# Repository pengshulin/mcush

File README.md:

DESCRIPTION
===========
* MCUSH is the short name for MCU-SHell.
* A practical project that enhance microcontroller serial port console with shell features like in many linux systems.
* The goal of the project is to provide a firmware template that will expand commands for new applications, so it should be designed with simple API and easy to use.
* Initially developed on FreeRTOS, but with os abstract layer, MCUSH has been ported to other RTOSes.
* The core shell runs as a stand-alone task with middle level priority.
* Auxiliary micro service tasks can be chosen when you need, such as LED blinker, logger, soft-watchdog...
* Test suites and templates written in python are privided to ease the test work and create CLI/GUI applications.
* Hosted on github: <https://github.com/pengshulin/mcush>
* Python core module released on PYPI and installed by 'pip3 install mcush'

FEATURES
========
* SUPPORT:
  * command functions are called with arguments in form of argc and argv
  * arguments parser with short option '-' and long option '--'
  * low memory requirement, suitable for some tiny chips
  * prompt hook function for customize
  * compact history command list
  * multi-line input
  * may port to different architectures, but currently it runs on CORTEX-M only
* NOT SUPPORT:
  * lineedit features that require multi-bytes (such as array keys, shell colors...) are not supported, only simple features that require single-byte (such as BACKSPACE, Ctrl-A/B/C/D/E/F/K/N/P) are supported

ROADMAP
=======
(todo/in progress)
* add threadx/chibios/liteos/zephyr/osek port
* test embedded dynamic languages (eg. lua/picolisp/tinyscheme/ulisp/micropython...)
* add practical utilities, such as network (traceroute, ntp client...)

ENVIRONMENT
===========
* arm-none-eabi-gcc, newlibc, arm-none-eabi-gdb, cgdb
* scons + personal MCU build scripts
  <https://github.com/pengshulin/site_scons>
* STLink v2 + st-flash(flasher) + st-util(gdb server)
  <https://github.com/texane/stlink>
* openocd
* develope and test on Debian/Ubuntu machines

RESOURCES
=========
* Snapshots: <https://github.com/pengshulin/mcush/tree/master/snapshots> 
* Demo videos: <https://github.com/pengshulin/mcush/tree/master/demo_video>  Suitable for beginners and give you a brief overview.
* Windows/VCP(Virtual Com Port) driver: <https://github.com/pengshulin/mcush/tree/master/vcp_driver>

HARDWARE
========
* tiny controller: <https://github.com/pengshulin/mcush/tree/master/hardware_tiny>
* Shell-Lab series controllers: <http://www.linkongsoft.com/shell-lab/>
* Vibration Analysis Platform: <http://www.linkongsoft.com/vap/>

LICENSE
=======
* source codes:
  * As this is my personal software toolkit, you can use it freely only for non-commercial purpose.
  * Contact the author for commercial authorization, or it's NOT AUTHORIZED.
* binary executables:
  * images provided in build directory are free as BSD
* hardware design files:
  * similar to the source codes: need commercial authorization

COMMERCIAL
==========
Contact Shanghai Linkong Software Technologies Co., Ltd for commerical support.
http://www.linkongsoft.com/

AUTHOR
======
Peng Shulin <trees_peng@163.com>
Shanghai, China 2022

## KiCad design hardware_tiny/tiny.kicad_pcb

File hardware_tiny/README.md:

RESOURCES
=========
* Demo videos: <https://github.com/pengshulin/mcush/tree/master/demo_video>
* Windows/VCP(Virtual Com Port) driver: <https://github.com/pengshulin/mcush/tree/master/vcp_driver>
* Schematic: <https://github.com/pengshulin/mcush/blob/master/hardware_tiny/tiny.pdf>
* Latest firmware: <https://github.com/pengshulin/mcush/tree/master/hardware_tiny/build>

LICENSE
=======
* see the project LICENSE

AUTHOR
======
Peng Shulin <trees_peng@163.com>
Shanghai, China 2018

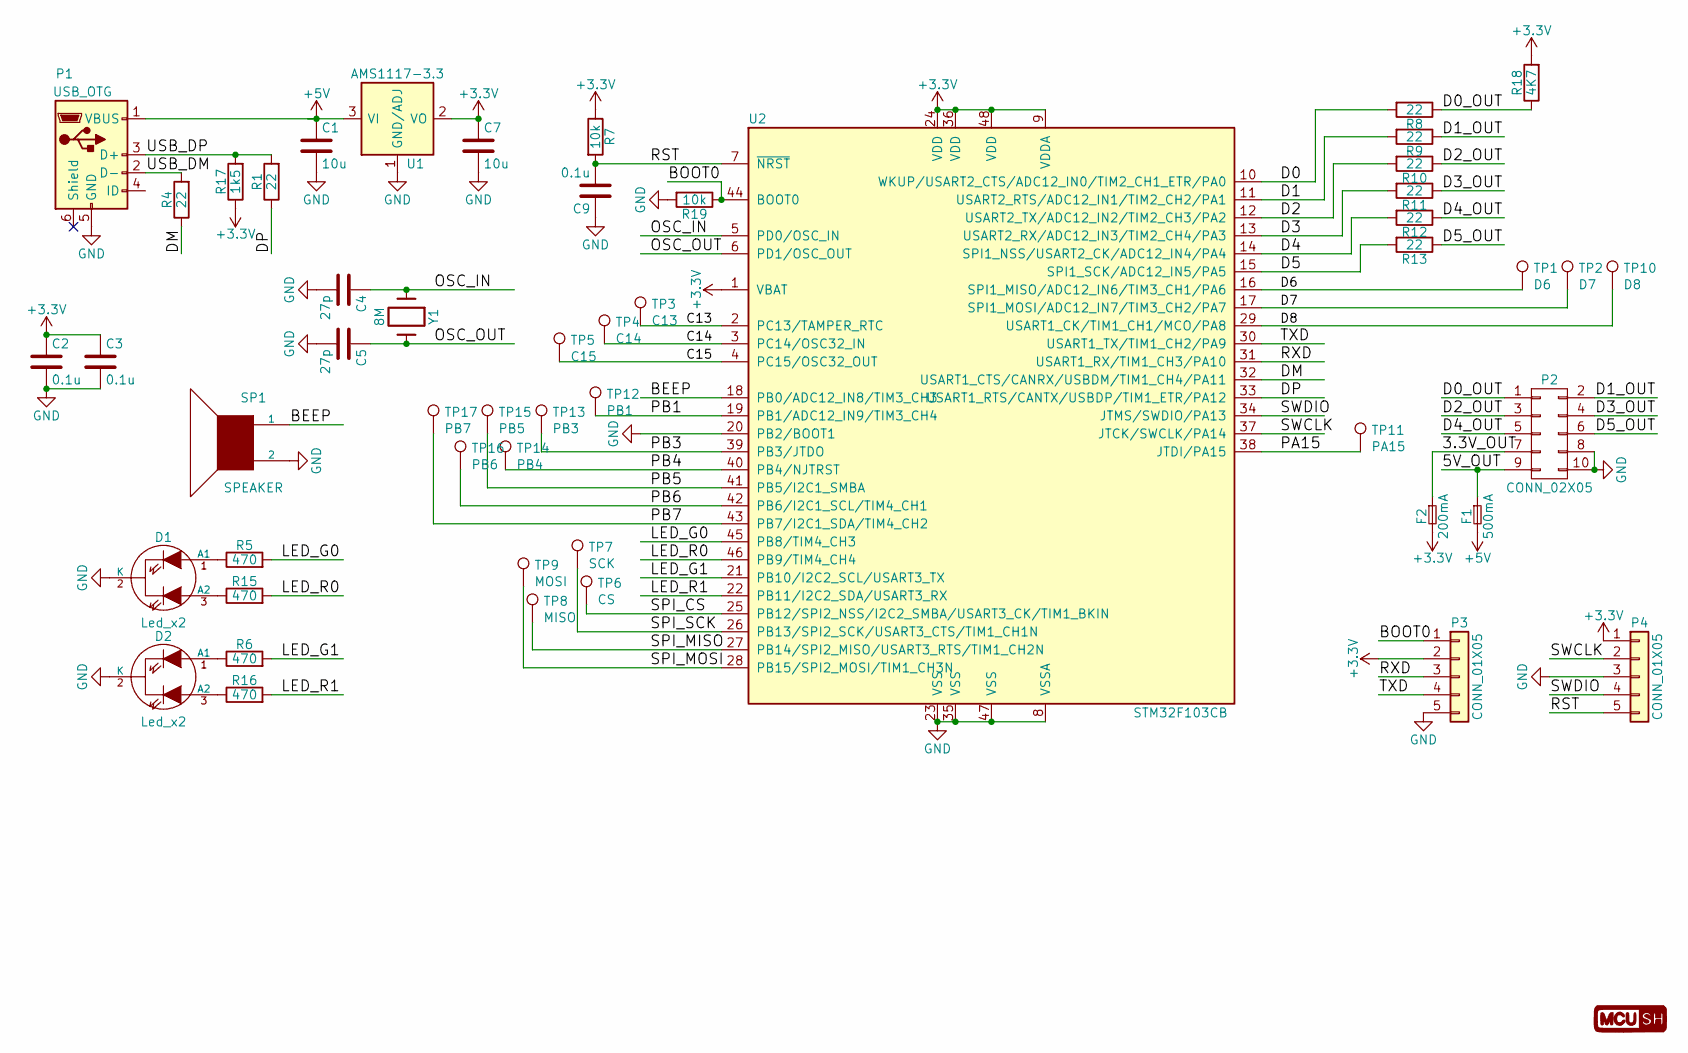
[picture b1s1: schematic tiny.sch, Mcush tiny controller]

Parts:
C1, C7: 10u; C_1210_3225Metric_Pad1.42x2.65mm_HandSolder
C2, C3, C9: 0.1u; C_0805_2012Metric_Pad1.15x1.40mm_HandSolder
C4, C5: 27p; C_0805_2012Metric_Pad1.15x1.40mm_HandSolder
D1, D2: Led_x2; LEDx2-3MM
F1: 500mA; R_1210_3225Metric_Pad1.42x2.65mm_HandSolder
F2: 200mA; R_1210_3225Metric_Pad1.42x2.65mm_HandSolder
LOGO1: MCUSH; mcush_txt_logo
P1: USB_OTG; USB_Mini-B_HandSoldering
P2: CONN_02X05; IDC10-E
P3, P4: CONN_01X05; PinHeader_1x05_P2.54mm_Vertical
R1, R4, R8, R9, R10, R11, R12, R13: 22; R_0805_2012Metric_Pad1.15x1.40mm_HandSolder
R5, R6, R15, R16: 470; R_0805_2012Metric_Pad1.15x1.40mm_HandSolder
R7, R19: 10k; R_0805_2012Metric_Pad1.15x1.40mm_HandSolder
R17: 1k5; R_0805_2012Metric_Pad1.15x1.40mm_HandSolder
R18: 4K7; R_0805_2012Metric_Pad1.15x1.40mm_HandSolder
SP1: SPEAKER; Buzzer_9x4.2RM4
TP1: D6; TestPoint_Pad_D1.0mm
TP2: D7; TestPoint_Pad_D1.0mm
TP3: C13; TestPoint_Pad_D1.0mm
TP4: C14; TestPoint_Pad_D1.0mm
TP5: C15; TestPoint_Pad_D1.0mm
TP6: CS; TestPoint_Pad_D1.0mm
TP7: SCK; TestPoint_Pad_D1.0mm
TP8: MISO; TestPoint_Pad_D1.0mm
TP9: MOSI; TestPoint_Pad_D1.0mm
TP10: D8; TestPoint_Pad_D1.0mm
TP11: PA15; TestPoint_Pad_D1.0mm
TP12: PB1; TestPoint_Pad_D1.0mm
TP13: PB3; TestPoint_Pad_D1.0mm
TP14: PB4; TestPoint_Pad_D1.0mm
TP15: PB5; TestPoint_Pad_D1.0mm
TP16: PB6; TestPoint_Pad_D1.0mm
TP17: PB7; TestPoint_Pad_D1.0mm
U1: AMS1117-3.3; SOT-223-3_TabPin2
U2: STM32F103CB; LQFP-48_7x7mm_P0.5mm
Y1: 8M; Crystal_HC49-U_Vertical

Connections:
+3V3: C2.1, C3.1, C7.1, F2.2, P3.2, P4.1, R7.1, R17.1, R18.2, U1.2 (VO), U2.1 (VBAT), U2.9 (VDDA), U2.24 (VDD), U2.36 (VDD), U2.48 (VDD)
+5V: C1.1, F1.2, P1.1 (VBUS), U1.3 (VI)
/3.3V_OUT: F2.1, P2.7
/5V_OUT: F1.1, P2.9
/BEEP: SP1.1, U2.18 (PB0/ADC12_IN8/TIM3_CH3)
/BOOT0: P3.1, R19.1, U2.44 (BOOT0)
/C13: TP3.1, U2.2 (PC13/TAMPER_RTC)
/C14: TP4.1, U2.3 (PC14/OSC32_IN)
/C15: TP5.1, U2.4 (PC15/OSC32_OUT)
/D0: R8.2, U2.10 (WKUP/USART2_CTS/ADC12_IN0/TIM2_CH1_ETR/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)
/D0_OUT: P2.1, R8.1, R18.1
/D1: R9.2, U2.11 (USART2_RTS/ADC12_IN1/TIM2_CH2/PA1)
/D1_OUT: P2.2, R9.1
/D2: R10.2, U2.12 (USART2_TX/ADC12_IN2/TIM2_CH3/PA2)
/D2_OUT: P2.3, R10.1
/D3: R11.2, U2.13 (USART2_RX/ADC12_IN3/TIM2_CH4/PA3)
/D3_OUT: P2.4, R11.1
/D4: R12.2, U2.14 (SPI1_NSS/USART2_CK/ADC12_IN4/PA4)
/D4_OUT: P2.5, R12.1
/D5: R13.2, U2.15 (SPI1_SCK/ADC12_IN5/PA5)
/D5_OUT: P2.6, R13.1
/D6: TP1.1, U2.16 (SPI1_MISO/ADC12_IN6/TIM3_CH1/PA6)
/D7: TP2.1, U2.17 (SPI1_MOSI/ADC12_IN7/TIM3_CH2/PA7)
/D8: TP10.1, U2.29 (USART1_CK/TIM1_CH1/MCO/PA8)
/DM: R4.1, U2.32 (USART1_CTS/CANRX/USBDM/TIM1_CH4/PA11)
/DP: R1.1, U2.33 (USART1_RTS/CANTX/USBDP/TIM1_ETR/PA12)
/LED_G0: R5.2, U2.45 (PB8/TIM4_CH3)
/LED_G1: R6.2, U2.21 (PB10/I2C2_SCL/USART3_TX)
/LED_R0: R15.2, U2.46 (PB9/TIM4_CH4)
/LED_R1: R16.2, U2.22 (PB11/I2C2_SDA/USART3_RX)
/OSC_IN: C4.1, U2.5 (PD0/OSC_IN), Y1.1
/OSC_OUT: C5.1, U2.6 (PD1/OSC_OUT), Y1.2
/PA15: TP11.1, U2.38 (JTDI/PA15)
/PB1: TP12.1, U2.19 (PB1/ADC12_IN9/TIM3_CH4)
/PB3: TP13.1, U2.39 (PB3/JTDO)
/PB4: TP14.1, U2.40 (PB4/NJTRST)
/PB5: TP15.1, U2.41 (PB5/I2C1_SMBA)
/PB6: TP16.1, U2.42 (PB6/I2C1_SCL/TIM4_CH1)
/PB7: TP17.1, U2.43 (PB7/I2C1_SDA/TIM4_CH2)
/RST: C9.2, P4.5, R7.2, U2.7 (~NRST)
/RXD: P3.3, U2.31 (USART1_RX/TIM1_CH3/PA10)
/SPI_CS: TP6.1, U2.25 (PB12/SPI2_NSS/I2C2_SMBA/USART3_CK/TIM1_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)
/SPI_MISO: TP8.1, U2.27 (PB14/SPI2_MISO/USART3_RTS/TIM1_CH2N)
/SPI_MOSI: TP9.1, U2.28 (PB15/SPI2_MOSI/TIM1_CH3N)
/SPI_SCK: TP7.1, U2.26 (PB13/SPI2_SCK/USART3_CTS/TIM1_CH1N)
/SWCLK: P4.2, U2.37 (JTCK/SWCLK/PA14)
/SWDIO: P4.4, U2.34 (JTMS/SWDIO/PA13)
/TXD: P3.4, U2.30 (USART1_TX/TIM1_CH2/PA9)
/USB_DM: P1.2 (D-), R4.2
/USB_DP: P1.3 (D+), R1.2, R17.2
GND: C1.2, C2.2, C3.2, C4.2, C5.2, C7.2, C9.1, D1.2 (K), D2.2 (K), P1.5 (GND), P2.8, P2.10, P3.5, P4.3, R19.2, SP1.2, U1.1 (GND/ADJ), U2.8 (VSSA), U2.20 (PB2/BOOT1), U2.23 (VSS), U2.35 (VSS), U2.47 (VSS)
unnamed: D1.1 (A1), R5.1
unnamed: D1.3 (A2), R15.1
unnamed: D2.1 (A1), R6.1
unnamed: D2.3 (A2), R16.1

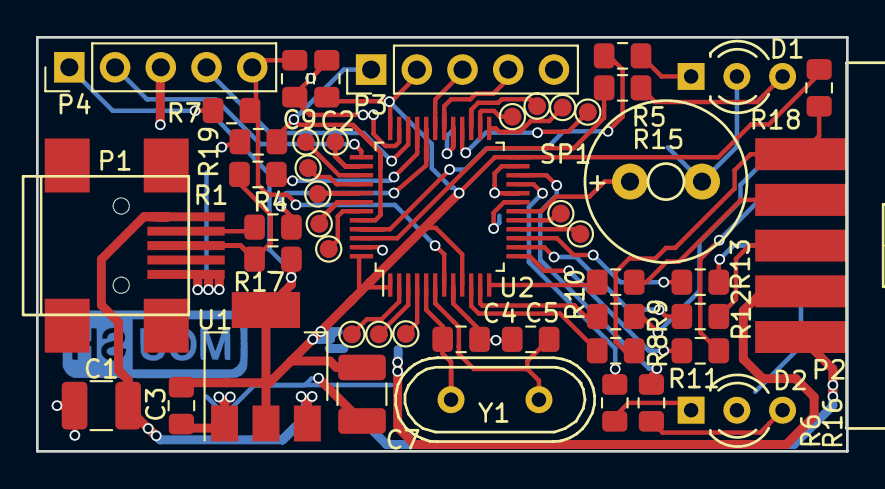
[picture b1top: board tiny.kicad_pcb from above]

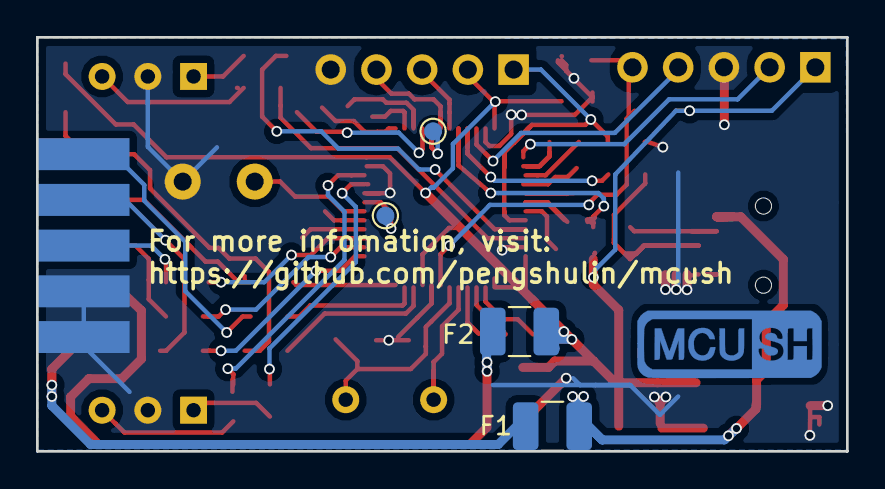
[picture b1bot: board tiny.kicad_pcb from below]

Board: 2 copper layers, 45.0 x 23.0 mm, 53 parts (5 on the bottom side), 55 nets.

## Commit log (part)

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2018-01-16 add: tjc hmi updater script
2018-01-18 edit
2018-02-13 add fcfs (Flash Configuration File System)
2018-02-23 fix the missing core direcotries
2018-03-06 fixbug: stm32f429ig flash 2M -> 1M actually
2018-03-07 fixbug: cat command, read mode, missing newline before prompt conditionally
2018-03-27 add shell_str.c
2018-05-02 add demo videos
2018-05-05 add resources url in readme
2018-05-07 add test max7219 script and demo video
2018-05-07 fix the spelling mistake
2018-05-09 add quoted arguments demo video
2018-05-12 add: hardware_usb_stick
2018-05-12 add build image for hardware_tiny board
2018-05-22 add cross build demo video
2018-06-20 add: appLwipDemo for stm32f407
2018-06-20 add: halstm32f207
2018-06-26 add customized scpi_idn mode
2018-06-27 add parson library
2018-07-05 add wget command
2018-07-07 edit: optimize opt_spec structure to reduze flash size
2018-07-12 edit:fix bugs checked by new gcc toolchain (imtroduced in ubuntu18.04
2018-07-13 edit:halt api optimize
2018-07-13 edit:remove all NON_OS feature
2018-07-13 fixbug:ENTER_CRITICAL before halt
2018-07-15 adapt for her scons api
2018-07-23 fixbug: opt parser for OPT_VALUE when USAGE_VALUE_REQUIRED is not set
2018-07-24 add: logger apis
2018-07-31 add: halstm32f103rb_nucleo
2018-08-10 add: lib crc and utils
2018-08-11 edit:add i2c lsb/nostop options and tested on tm1637 led controller
2018-08-13 fix: usb descriptor serial number sequence
2018-08-29 add_feature: check if command exists
2018-09-08 add tm1637 demo video
2018-09-14 add pwm/dxw90 micro servo demo
2018-09-20 add adc/pwm control
2018-10-06 add partial functions for gpio control
2018-10-10 add Dallas 1wire control; Tri-color LED control
2018-10-13 add official ST VCP v1.5.0
2018-10-16 add hardware tiny controller brocher
2018-10-19 add shell_call api
2018-10-26 add: HAL/LL Driver for STM32F4/7
2018-10-29 edit: rearrange the hal layer structure for better expandiability
2018-10-31 fixbug: hal_gpio/usart using ST/F1xx/HAL driver
2018-12-14 new logger policy
2018-12-17 edit: logger module use mutex for file manipulate
2018-12-18 fixbug: use spiffs_lock/unlock
2018-12-19 fixbug: deleted spiffs semaphore is invalid when format
2018-12-21 fixbug:logger line buffer too small to hold large contents
2018-12-24 edit: less malloc/free for log -t command
2018-12-27 fix: set_rtc_by_XXX accepts year in 2-digit; sys trace buffer bigger
2018-12-29 fixbug: dhcpc queue blocked
2019-01-01 add: sys idle_check/vfs_stat command; optimize: spiffs fd/cache size; fix: vfs open/close reentrance problem; optimize: app_logger lazy close
2019-01-01 add: some filesystem test scripts
2019-01-03 fixbug: increase local port for next tcp_bind
2019-01-03 fix: dhcpc discover timeout retry; add: net up/down/dhcp command
2019-01-05 add: logger new apis; lwip debug/logger; sprintf api with half integer feature; edit: lwip_bind_random ports rfc range
2019-01-06 edit: use native dhcp controller; add: netbiosns interface; fix: lwip_stats output directly to shell; edit: printf2 add hx/hX support;
2019-01-09 add: Mcush/wget function; lwip MEM_LIBC_MALLOC option defination;
2019-01-09 edit: set default MEM_MALLOC as lwip
2019-01-10 add: test wget command looply
2019-01-10 add: nc cmd for tcp debug;
2019-01-11 fix: clear wdg every digit blink; fix: wrong elf file searched in release mode; edit: increase default mcush stack
2019-01-11 optimize: cache nc send buffer for effeciency;
2019-01-14 fix: encoding err; edit: unified pdPASS return of QueueSend/Receive apis; change lan8742a delay function to rtos delay;
2019-01-18 add: configuration macro
2019-01-24 fix: release data bus on first half phrase when i2c read address ACK
2019-03-05 add: crc32 file check
2019-04-10 add spiflash chipid; add HAL_TEST_CLK_OUTPUT macro
2019-04-12 add modbus/tcp framework and demo hook functions
2019-04-29 add modbus/tcp features
2019-04-30 add_feature: modbus/tcp coil functions support
2019-05-06 fix: add timeout check for modbus/tcp connect (lazy check)
2019-05-13 fixbug: file not closed for crc check
2019-05-17 add one-wire for stm32f4; optimize rtc init policy
2019-06-05 update to FreeRTOS v10.2.1; add missing files
2019-06-18 edit: basic str translation embedded; add compare_functions
2019-06-24 add: fastlz lib
2019-07-10 add: alink test; ld scripts; edit rtc init algorithms; fix bugs
2019-07-11 optimze lan7820 driver; user sprintf_ip/mac api instead of logger_ip/mac
2019-07-14 add: alink readme/license file; fix some bugs
2019-07-23 add log_mon script
2019-08-02 fix: opt parse bug for single - parm condition; update debug utils
2019-08-07 optimize apis: shell_eval_xxx --> parse_xxx; split_line/strip_line; file_load_xxx;
2019-08-07 add switch random script
2019-08-20 add: lua gpio/log module
2019-08-31 add cmd option to dynamically edit dns; python module modification for Python v3; add python ledSet/Clr api; etc
2019-09-07 optimize lua module api
2019-09-09 fixbug: lua test example
2019-09-17 add missing libfatfs/source
2019-09-17 add fatfs port
2019-09-20 support multiple emulated spi modules
2019-09-24 add multi emulated i2c controllers support; fix _open return code on file error
2019-10-04 add stm32f429x_sdram.ld; fixbug for 32MBytes spiflash; ...
2019-10-04 add pre-built image for stm32f103c8 tiny boards
2019-10-08 add pulse generator command
2019-10-10 fix: led signal invert for board f103rc_mcudev
2019-10-10 add pre-built image for f103cb_tiny_controller; add step motor test script
2019-10-14 optimize i2c timing
2019-10-14 add SSD1306 controller and test script
2019-10-16 remove ds1w alias command
2019-10-20 emu_spi timing optimized; add MAX6675/TM7707 module; rebuild images
2019-10-22 rebuild images and remove .map files
2019-10-25 add AHT10 module; add max7219 8digits LED diaplay module; ...
2019-10-27 switch from py2exe to pyinstaller; add tag v1.4.3
2019-11-02 add instruments modules (fluke/keysight/uni_trend...); fix Aht10 bugs
2019-11-04 add FY6900 signal generator controller
2019-11-05 add meas/counter/sweep api for FY6900 module
2019-11-06 add Max30102 module
2019-11-07 add Ads1115 module
2019-11-10 optimzie shell lab api
2019-11-13 optimize F8808A apis
2019-11-24 add stm32f401cc/411ce WeAct board support
2019-11-24 add build images for stm32f401/411 WeAct boards
2019-12-05 add Korad/KA3005P 30V/5A power output
2019-12-06 fixbug: ka3005p output enable/disable api parms
2019-12-10 add rigol products templates
2020-01-13 add RIGOL/DS1000 Oscillator support
2020-02-13 add hal_key apis; add can baudrate api; add filter set command
2020-03-06 update ST_USB_FS_Device_Driver; ...
2020-03-17 add CAN drivers; update README for commerical support
2020-03-17 add libCanFestival
2020-04-01 spiffs chip-id optimize; add status read cmd; add Instrument class terminal_reset init option; add logger busy check api; ...
2020-04-10 add static task/queue create api; add support for stm32f030c8 tiny board; add python module Tongmen programmable power; ...
2020-04-20 fix: cache vcp linecoding setting (pyserial may raise exception in windows); optimize CAN api; add usb string descriptor configuration api from SConstruct; ...
2020-04-23 add ws2812 library and command; fixbug in fluke/f5520, print syntax in python v3; add missing files...
2020-04-24 fix: UniqueID address for stm32f030; default port/pin defination for ws2812 command
2020-04-26 optimize ws2812 apis
2020-04-27 add FCFS program api
2020-05-08 add enumPortsByClass api; ...
2020-05-08 fixbug: enumPortsByClass did not free serial port when IDNMatch error occurs
2020-05-10 optimize: use two default filters to receive all STD/EXT-ID frames; fix: check for Ctrl-C in can read command or *idn? may not work;
2020-05-13 fixbug for python3
2020-05-18 fixbug for Python V3
2020-05-18 add openocd/telnet api template
2020-05-19 add OpenOCD apis
2020-05-19 fixbug for pip setup.py
2020-05-26 optimize ws2812 push command and add fill command
2020-06-01 fixbug: stm32f103 hal/vcp driver; rebuild binaries; ...
2020-06-02 add ST/F0_HAL_Driver
2020-06-04 rename macro HAL_RESET_VCP_PIN -> HAL_RESET_USB_PINS
2020-06-15 optimize python api; remove crcmod module dependency
2020-06-15 add serial_send_bytes test script
2020-06-16 fixbug: ds1w/motion be compatiable in python v3
2020-06-26 add python readLine/writeCommand strip options
2020-07-16 add RTOS Abstract Layer; update STM32F7 HAL lib; add python lib for Miaoguan 485 Sensor
2020-07-17 impove RTOS Abstract Layer
2020-07-19 update CMSIS/lib; optimize OS Abstract Layer (split mutex from semaphore); add RTX port
2020-07-20 port RTOS Abstract Layer
2020-08-08 update CMSIS lib; add compiler port file; add more compiler check and fix those warnings; ...
2020-08-09 fix compiler warnings
2020-08-14 continue to port RTThread...
2020-08-17 add blink errno task brief instruction
2020-09-10 add mcush_os_none.h for special build condition(eg.bootloader); optimize ws2812 api; optimize logger.c build for when SPIFFS not supported; ...
2020-09-10 add libmd5 from lua/md5 projdct
2020-09-27 fixbug: script load command
2020-09-28 rebuild images for demo boards
2020-10-12 optimize os ports; optimize hal_gpio apis; remove wdg cmd; add (err)stop for script loading; add shortname check for help cmd;add down count option for lamp/strap python api; ...
2020-10-12 use independent basic hal api header file
2020-10-12 add missing documents
2020-10-13 fix: ignore timer_queue_overflow error for rtx port, or sys idle command will not work
2020-10-27 add python rotate mode control for ShellLabLamp
2020-11-25 add_lib: Mlx90614/ShellLabStepperMotor; optimize beep service task
2020-12-11 add WitMotion Python module
2020-12-19 add MindMotion MM32F031 support
2020-12-25 edit: reduce ws2812 buffer size; add sht30 sensor; add ShellLabSegmentDisplay support; ...
2021-02-19 add lpc43xx basic hal driver
2021-03-05 add GCode module to support Marlin firmware
2021-04-15 add inverse option for test command; rename Strap class to Strip; fixbug for FCFS/File in bytes mode; add new OS options; ...
2021-04-21 add MCUSH device API/C
2021-05-22 rebuild binaries; add device api for win32 support; ...
2021-05-22 add device/c api demoes
2021-05-24 add s1_relay_ctrl c/api demo
2021-06-06 fix parse_int error returns; add C/API test demo; add python SpotLightController module; update Ws2812 api;...
2021-06-12 add mcush_drv C++ driver and demo
2021-06-15 add Pca9685 module; add mcush_utils feature
2021-06-16 add mcush_util.dll build
2021-07-13 fix: CANOpen readObject command code
2021-08-21 add SN->MAC hash convert; redesign modbus/tcp data structure; modify VAP api; add RIGOL DG1022Z; fixbugs...
2021-08-22 modify blink errno reserved id; fix bugs ...
2021-09-02 update sys_arch_mcush for lwip; add heap check option for lwip cmd; replace address printf from %X to %p; modbus_tcp packet handler move to callback functions; ...
2021-09-02 add lwip/contrib-2.0.1
2021-09-12 move task_blink/logger/swdg into service directory
2021-09-15 add stm32g0xx support
2021-10-01 fix usb cdc/hid lib; add python modbus/sako/vap200-mqtt libs; ...
2021-10-13 add MCUSH software certification scan file
2021-11-16 add gpio pull-up/down for lpc845; add ShellLabHID class for simulator controller; add fast mode color switch for ShellLabLamp; add VAP200Extend; ...
2021-12-13 fixbug: F1/HAL; add:ShellLabKeySwitch Python class
2022-02-16 update libFreeRTOS to v10.4.6; update mcush_util
2022-02-17 update: mcush_util
2022-02-18 add_feature: mcush_util get_file and shell mode
2022-02-21 add:BH1750 ambient sensor; fixbug:i2c read without write; mcush_util shell mode disabled in win32
2022-02-21 rebuild
2022-02-25 add Python/Bh1750 module; update VAP200 extend board api
2022-03-01 rename task_dhcpc to task_netmon
2022-03-18 update modbus/rtu routine and rearrange common source/header codes
2022-03-19 add NO_SHELL compact mode test
2022-04-03 add mcush posix OS port
2022-04-03 edit: posix os port
2022-04-16 add posix LED/gpio visualizer
2022-04-24 add: ws2812 emulator
2022-05-02 fixbug: ptr/int64 parse error in posix/64 mode
2022-05-09 add ThreadX port, tested under stm32f412re platform
